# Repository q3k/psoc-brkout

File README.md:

A tiny, cheap breakout board for Cypress PSoC4200 44TQFP chips.

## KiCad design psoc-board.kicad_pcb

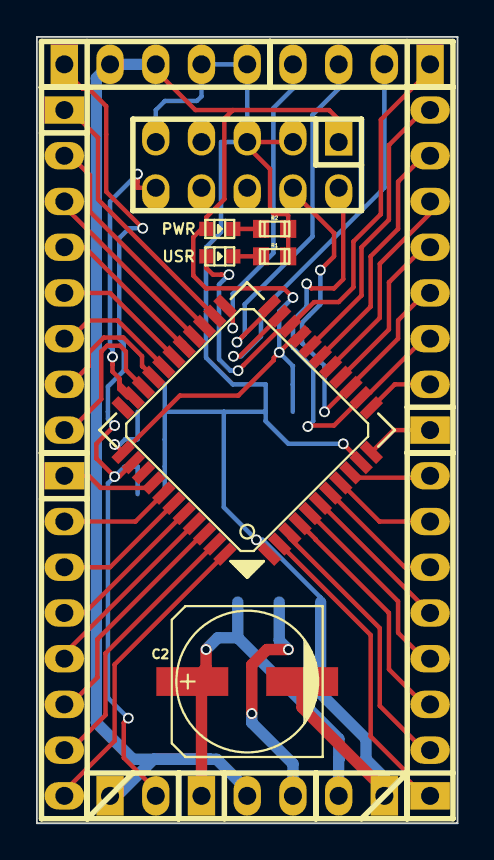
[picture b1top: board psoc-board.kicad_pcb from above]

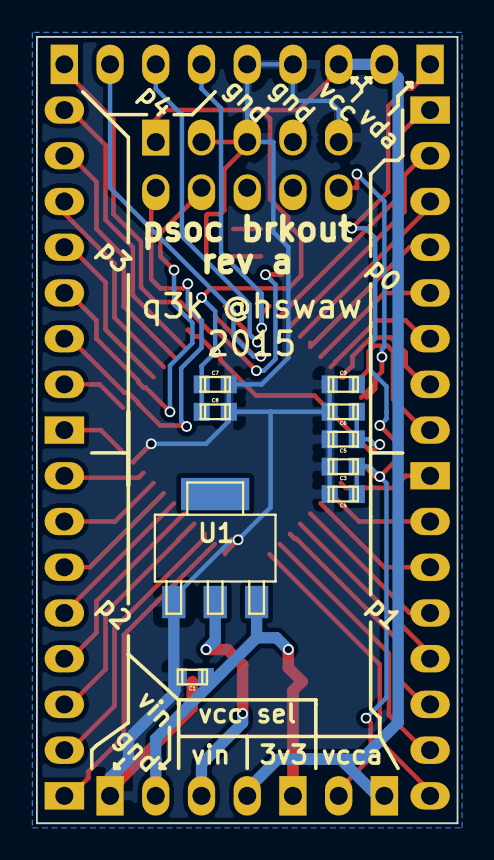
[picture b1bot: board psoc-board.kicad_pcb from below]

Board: 2 copper layers, 23.4 x 43.7 mm, 25 parts (9 on the bottom side), 45 nets.

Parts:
C1, C4, C6, C8, C9: 1uF; c_0603
C2: 47uF; c_elec_8x6.7
C3, C5, C7: 100nF; c_0603
J1: VIN; pin_strip_2
J2: VCCSEL; pin_strip_3
J3: VCCASEL; pin_strip_2
J4: PORT0; pin_strip_8
J5: PORT1; pin_strip_8
J6: POWER; pin_strip_5
J7: PORT2; pin_strip_8
J8: PORT3; pin_strip_8
J9: PORT4; pin_strip_4
LD1: USR; Led_0603
LD2: PWR; Led_0603
R1, R2: 330; r_0603
U1: LM1117-SOT; sot223
U2: ePSOC4200-44TQFP; lqfp44
eJ10: SWD; pin_socket_5x2

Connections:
/RESET: U2.32, eJ10.10
/SWDCLK: J8.4, U2.14, eJ10.4
/SWDIO: J8.3, U2.13, eJ10.2
/VDDA: C3.2, C4.2, J3.2, J6.1, U2.35
GND: C1.1, C2.2, C3.1, C4.1, C5.1, C6.1, C7.1, C8.1, C9.2, J1.1, J6.4, J6.5, R1.1, R2.1, U1.1, U2.1, U2.10, U2.36, eJ10.3, eJ10.5, eJ10.9
unnamed: C1.2, C2.1, J1.2, J2.1, U1.3
unnamed: C9.1, U2.33
unnamed: J2.3, U1.2, U1.4
unnamed: J4.1, U2.24
unnamed: J4.2, U2.25
unnamed: J4.3, U2.26
unnamed: J4.4, U2.27
unnamed: J4.5, U2.28
unnamed: J4.6, U2.29
unnamed: J4.7, U2.30
unnamed: J4.8, U2.31
unnamed: J5.1, U2.37
unnamed: J5.2, U2.38
unnamed: J5.3, U2.39
unnamed: J5.4, U2.40
unnamed: J5.5, U2.41
unnamed: J5.6, U2.42
unnamed: J5.7, U2.43
unnamed: J5.8, U2.44
unnamed: J7.1, U2.2
unnamed: J7.2, U2.3
unnamed: J7.3, U2.4
unnamed: J7.4, U2.5
unnamed: J7.5, U2.6
unnamed: J7.6, U2.7
unnamed: J7.7, U2.8
unnamed: J7.8, U2.9
unnamed: J8.1, U2.11
unnamed: J8.2, U2.12
unnamed: J8.5, U2.15
unnamed: J8.6, U2.16
unnamed: J8.7, U2.17
unnamed: J8.8, U2.18
unnamed: J9.1, LD1.1, U2.20
unnamed: J9.2, U2.21
unnamed: J9.3, U2.22
unnamed: J9.4, U2.23
unnamed: LD1.2, R1.2
unnamed: LD2.2, R2.2
VCC: C5.2, C6.2, C7.2, C8.2, J2.2, J3.1, J6.2, J6.3, LD2.1, U2.19, U2.34, eJ10.1

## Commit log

2015-09-12 Initial commit.
